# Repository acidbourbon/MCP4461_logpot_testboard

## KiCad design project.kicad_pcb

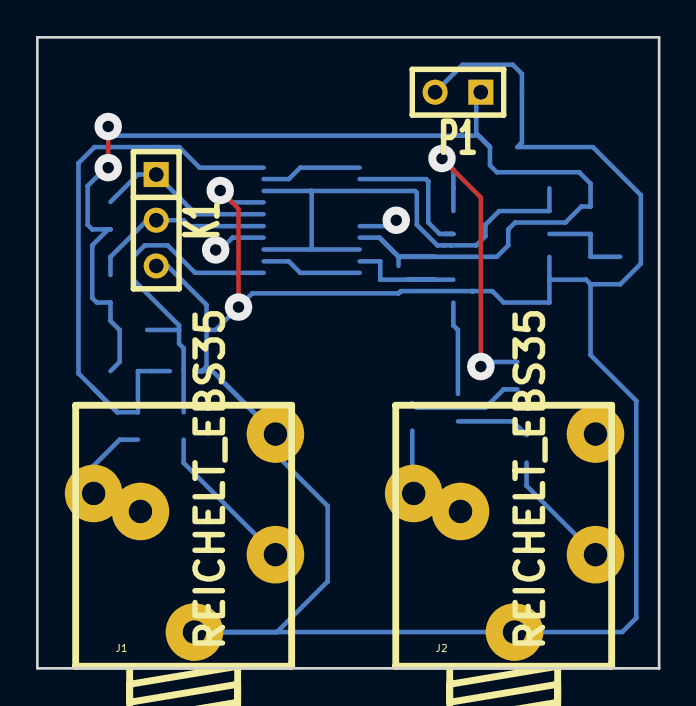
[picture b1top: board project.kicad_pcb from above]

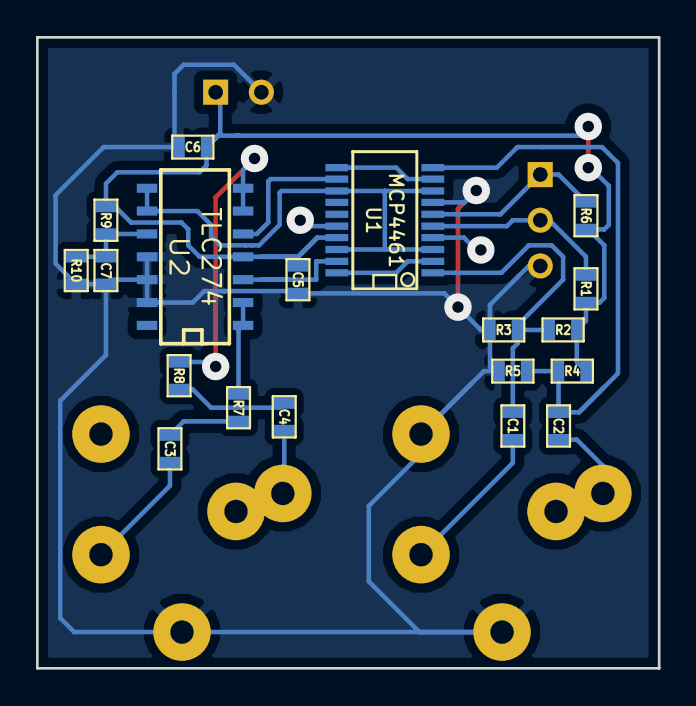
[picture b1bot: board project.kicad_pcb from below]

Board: 2 copper layers, 34.5 x 35.1 mm, 23 parts (19 on the bottom side), 20 nets.

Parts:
C1, C2: 1u; SM0603
C3, C4: 10u; SM0603
C5, C6, C7: 100n; SM0603
J1, J2: REICHELT_EBS35; Reichelt_EBS35
K1: CONN_3; SIL-3
P1: CONN_2; SIL-2
R1, R6, R9, R10: 10k; SM0603
R2, R3, R4, R5: 1M; SM0603
R7, R8: 220; SM0603
U1: MCP4461; SSOP20
U2: TLC274; SO14E

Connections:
/gnd: C5.2, C6.2, C7.2, J1.3, J2.3, K1.3, P1.2, R3.2, R5.2, R10.2, U1.7, U2.11, U2.12, U2.13
/in_L: C1.1, J1.1
/in_R: C2.1, J1.2
/out_L: C3.2, J2.1
/out_R: C4.2, J2.2
/scl: K1.2, R1.2, U1.5
/sda: K1.1, R6.2, U1.6
/vcc: C5.1, C6.1, P1.1, R1.1, R2.1, R4.1, R6.1, R9.1, U1.17, U2.4
/vcc/2: U1.3, U1.8, U1.13, U1.18, U2.8, U2.9
unnamed: R8.1, U2.6, U2.7
unnamed: C4.1, R8.2
unnamed: U1.19, U2.3
unnamed: U1.12, U2.5
unnamed: U1.9, U1.11
unnamed: R7.1, U2.1, U2.2
unnamed: C3.1, R7.2
unnamed: C7.1, R9.2, R10.1, U2.10
unnamed: U1.2, U1.20
unnamed: C1.2, R2.2, R3.1, U1.1
unnamed: C2.2, R4.2, R5.1, U1.10
